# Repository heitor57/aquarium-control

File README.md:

# aquarium-control
Aquarium controlled by PIC18F4550 with a program for Android to configure the respective MCU.

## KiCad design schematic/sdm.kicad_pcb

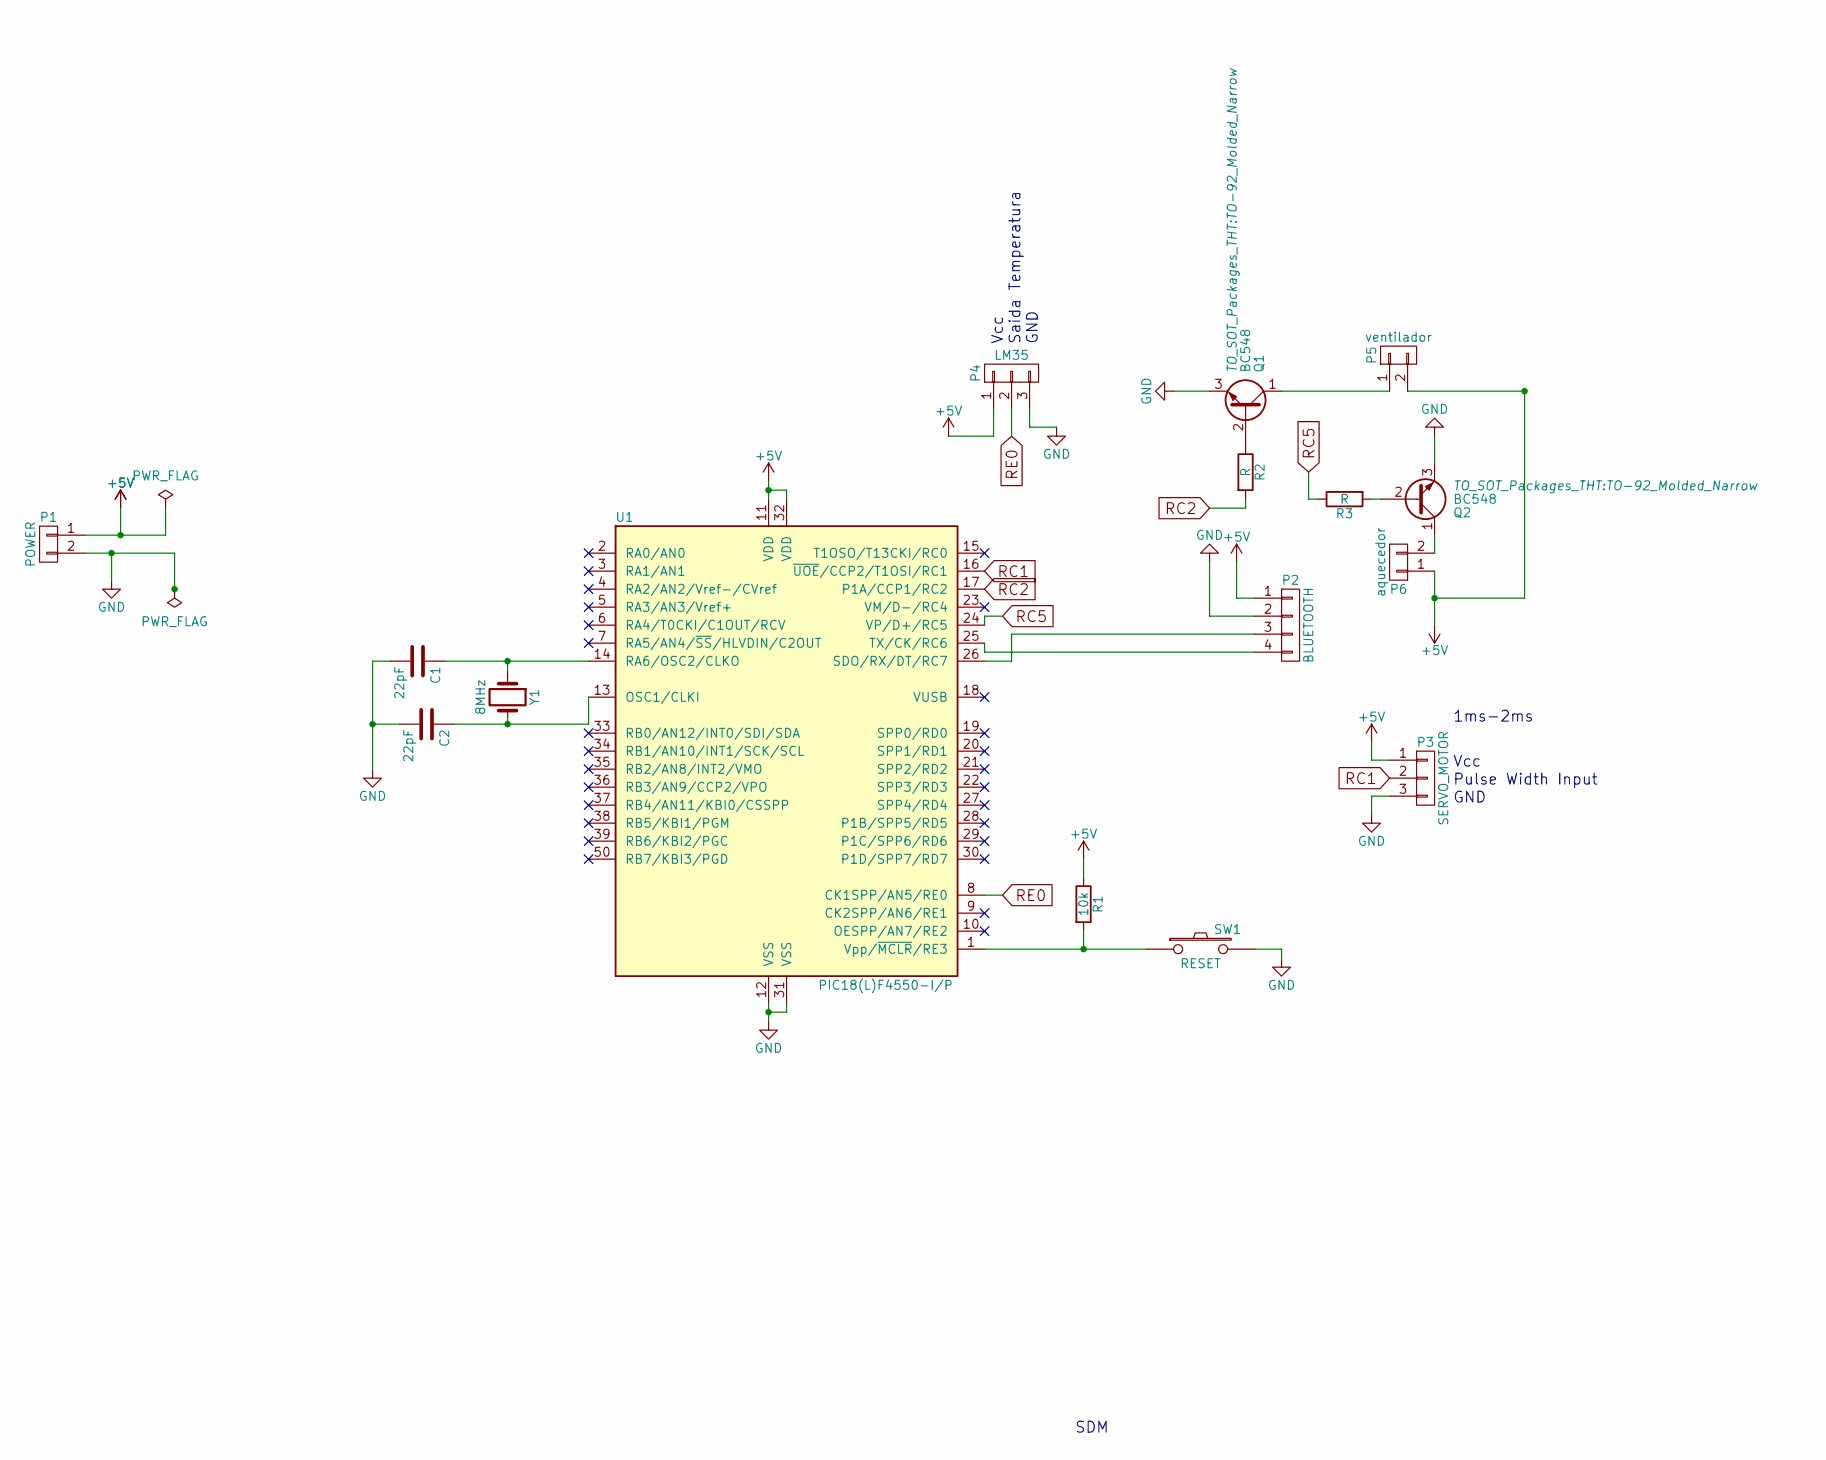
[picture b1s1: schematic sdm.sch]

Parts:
C1, C2: 22pF; C_Disc_D3.0mm_W2.0mm_P2.50mm
P1: POWER; Pin_Header_Straight_2x01_Pitch2.54mm
P2: BLUETOOTH; Socket_Strip_Straight_1x04_Pitch2.54mm
P3: SERVO_MOTOR; Pin_Header_Straight_1x03_Pitch2.54mm
P4: LM35; Socket_Strip_Straight_1x03_Pitch2.54mm
P5: ventilador; Pin_Header_Straight_2x01_Pitch2.54mm
P6: aquecedor; Pin_Header_Straight_2x01_Pitch2.54mm
Q1, Q2: BC548; TO-92_Molded_Narrow
R1: 10k; R_Axial_DIN0207_L6.3mm_D2.5mm_P15.24mm_Horizontal
R2, R3: R; R_Axial_DIN0207_L6.3mm_D2.5mm_P15.24mm_Horizontal
SW1: RESET; SW_SPST_FSMSM
U1: PIC18(L)F4550-I/P; DIP-40_W15.24mm_LongPads
Y1: 8MHz; Crystal_DS15_d1.5mm_l5.0mm_Vertical

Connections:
+5V: P1.1, P2.1, P3.1, P4.1, P5.2, P6.1, R1.1, U1.11 (VDD), U1.32 (VDD)
GND: C1.2, C2.2, P1.2, P2.2, P3.3, P4.3, Q1.3 (E), Q2.3 (E), SW1.2, U1.12 (VSS), U1.31 (VSS)
unnamed: C1.1, U1.14 (RA6/OSC2/CLKO), Y1.1
unnamed: C2.1, U1.13 (OSC1/CLKI), Y1.2
unnamed: P2.3, U1.26 (SDO/RX/DT/RC7)
unnamed: P2.4, U1.25 (TX/CK/RC6)
unnamed: P5.1, Q1.1 (C)
unnamed: P6.2, Q2.1 (C)
unnamed: Q1.2 (B), R2.1
unnamed: Q2.2 (B), R3.2
unnamed: R1.2, SW1.1, U1.1 (Vpp/~MCLR~/RE3)
RC1: P3.2, U1.16 (~UOE~/CCP2/T1OSI/RC1)
RC2: R2.2, U1.17 (P1A/CCP1/RC2)
RC5: R3.1, U1.24 (VP/D+/RC5)
RE0: P4.2, U1.8 (CK1SPP/AN5/RE0)

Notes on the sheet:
SDM
1ms-2ms
GND
Vcc
Pulse Width Input
Vcc Saida Temperatura GND

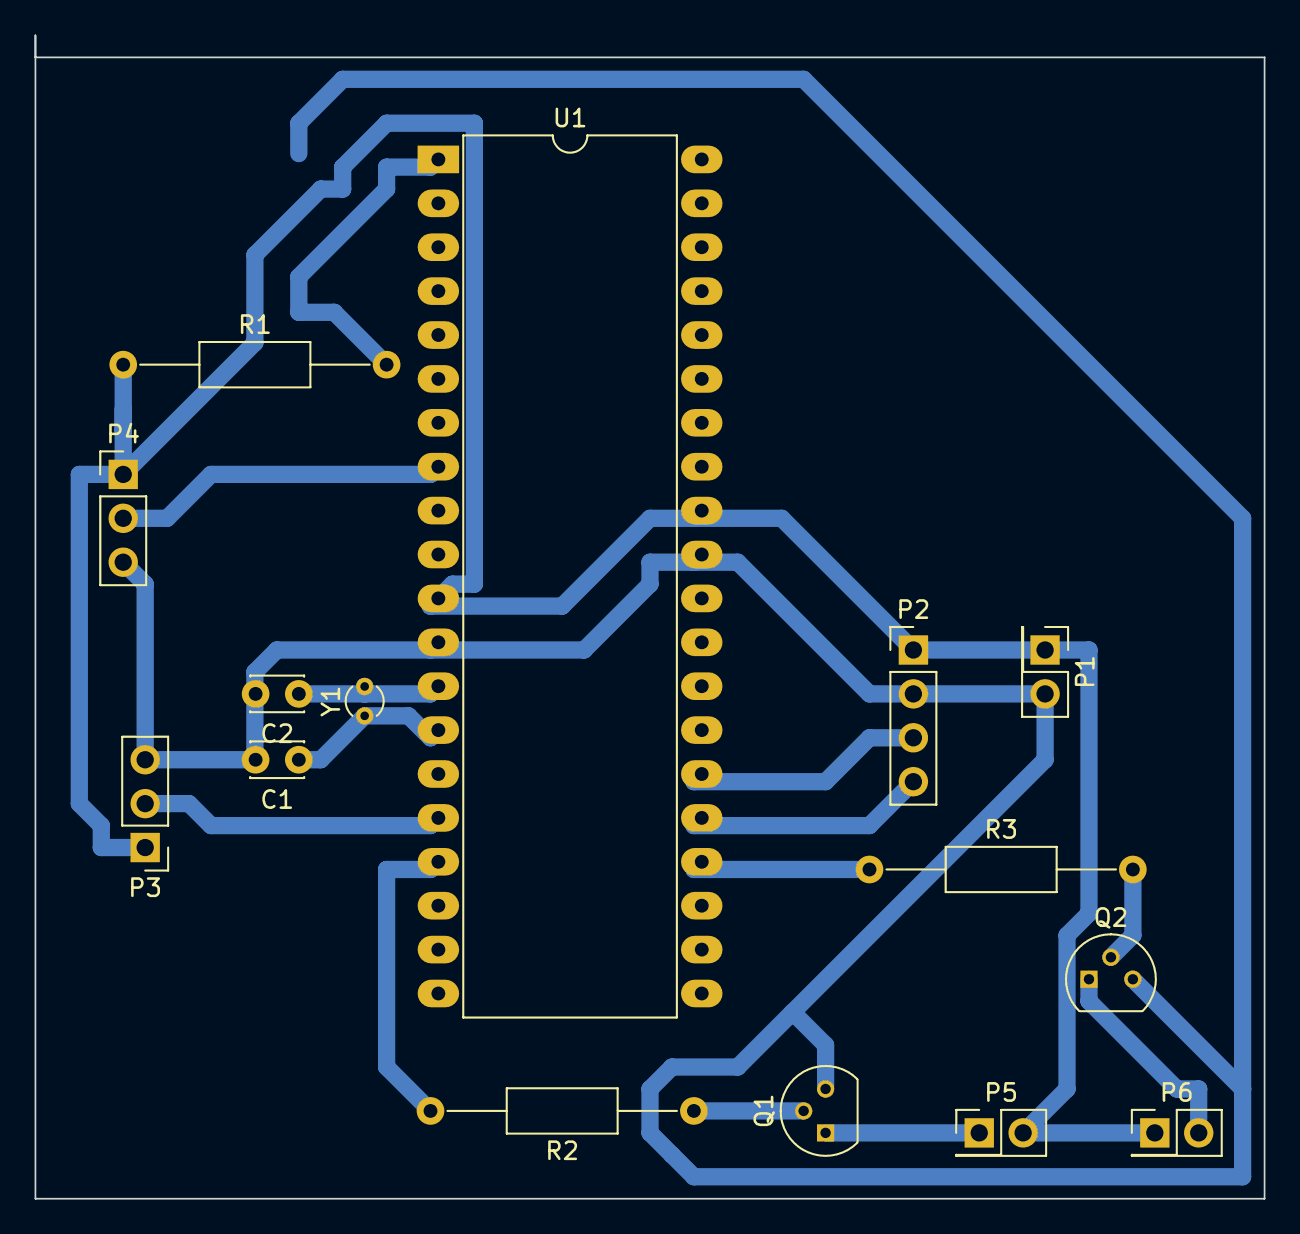
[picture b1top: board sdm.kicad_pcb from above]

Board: 2 copper layers, 71.1 x 67.3 mm, 16 parts (1 on the bottom side), 15 nets.

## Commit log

2017-10-14 pdf update
2017-10-14 Create LICENSE
2018-10-14 Update LICENSE
